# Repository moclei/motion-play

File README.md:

# Motion Play

ESP32-based sensor system for detecting and tracking fast-moving objects through a detection plane. Designed for games and sports performance training.

## Project Status

**Phase 4 - Integration & Polish** (77% complete)

- ✅ Custom PCBs with dual-MUX sensor architecture
- ✅ 1000 Hz data collection with PSRAM buffering
- ✅ AWS IoT Core + Lambda + DynamoDB backend
- ✅ React web interface with visualization and device control
- 🔄 Testing, optimization, documentation

## Repository Structure

```
motion-play/
├── .context/           # AI context documentation (start here)
│   ├── PROJECT.md      # Comprehensive project context
│   ├── manifest.yaml   # Structured metadata
│   └── IDEAS.md        # Feature backlog
├── firmware/           # ESP32-S3 firmware (PlatformIO/Arduino)
├── frontend/           # React web interface
├── lambda/             # AWS Lambda functions
├── infrastructure/     # AWS setup and deployment
├── hardware/           # KiCad PCB designs
│   ├── pcb-main/       # Main controller board
│   ├── sensor-rigid/   # Sensor rigid base (mux, connectors)
│   └── sensor-flex/    # Sensor flex strip (VCNL4040s)
└── docs/references/    # Hardware datasheets
```

## Quick Start

```bash
# Firmware
cd firmware && pio run -t upload

# Frontend
cd frontend/motion-play-ui && npm install && npm run dev
```

## Documentation

**For AI assistants and detailed context**: See [`.context/PROJECT.md`](.context/PROJECT.md)

**Hardware reference materials**: See [`docs/references/`](docs/references/)

## Hardware

- **MCU**: LilyGO T-Display-S3 (ESP32-S3)
- **Sensors**: 6× VCNL4040 proximity sensors (3 assemblies × 2 sensors)
- **Sensor Design**: Rigid+Flex hybrid PCBs (sensors on flex strip angle outward for better direction detection)
- **Architecture**: TCA9548A → PCA9546A → VCNL4040 (dual I2C multiplexing)

## License

[TBD]

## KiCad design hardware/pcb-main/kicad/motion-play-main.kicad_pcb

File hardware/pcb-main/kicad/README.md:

# motion-play-main
Main PCB for Motion Play project

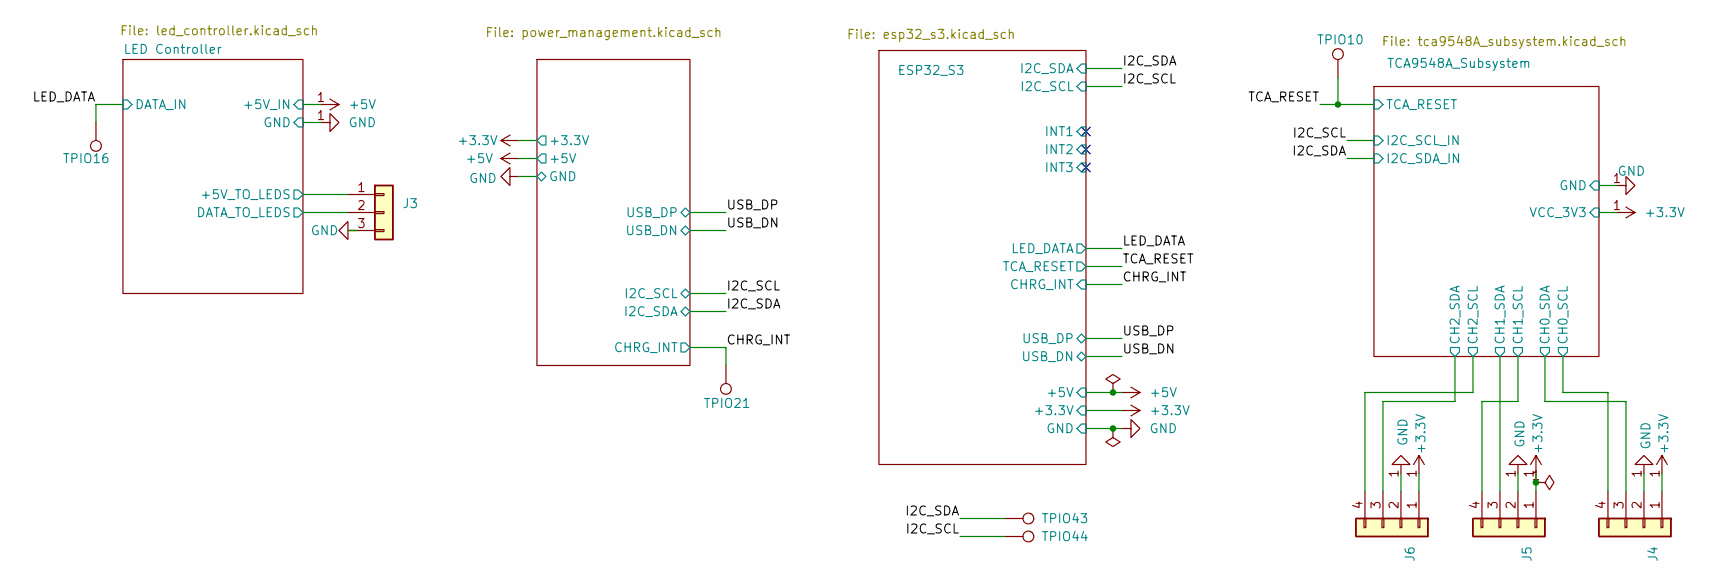
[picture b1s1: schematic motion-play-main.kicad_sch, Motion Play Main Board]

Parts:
J3: LED_Strip; JST_PH_S3B-PH-SM4-TB_1x03-1MP_P2.00mm_Horizontal; LCSC Part C265101
J4, J5, J6: Conn_01x04; JST_SH_SM04B-SRSS-TB_1x04-1MP_P1.00mm_Horizontal; LCSC Part No C160404
TPIO10, TPIO16, TPIO21, TPIO43, TPIO44: TestPoint; TestPoint_Pad_D2.0mm

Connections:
+3.3V: J4.1, J5.1, J6.1; also elsewhere on the board
/CHRG_INT: TPIO21.1; also elsewhere on the board
/I2C_SCL: TPIO44.1; also elsewhere on the board
/I2C_SDA: TPIO43.1; also elsewhere on the board
/LED Controller/+5V_TO_LEDS: J3.1; also elsewhere on the board
/LED Controller/DATA_TO_LEDS: J3.2; also elsewhere on the board
/LED_DATA: TPIO16.1; also elsewhere on the board
/TCA9548A_Subsystem/CH0_SCL: J4.4; also elsewhere on the board
/TCA9548A_Subsystem/CH0_SDA: J4.3; also elsewhere on the board
/TCA9548A_Subsystem/CH1_SCL: J5.4; also elsewhere on the board
/TCA9548A_Subsystem/CH1_SDA: J5.3; also elsewhere on the board
/TCA9548A_Subsystem/CH2_SCL: J6.4; also elsewhere on the board
/TCA9548A_Subsystem/CH2_SDA: J6.3; also elsewhere on the board
/TCA_RESET: TPIO10.1; also elsewhere on the board
GND: J3.3, J4.2, J5.2, J6.2; also elsewhere on the board

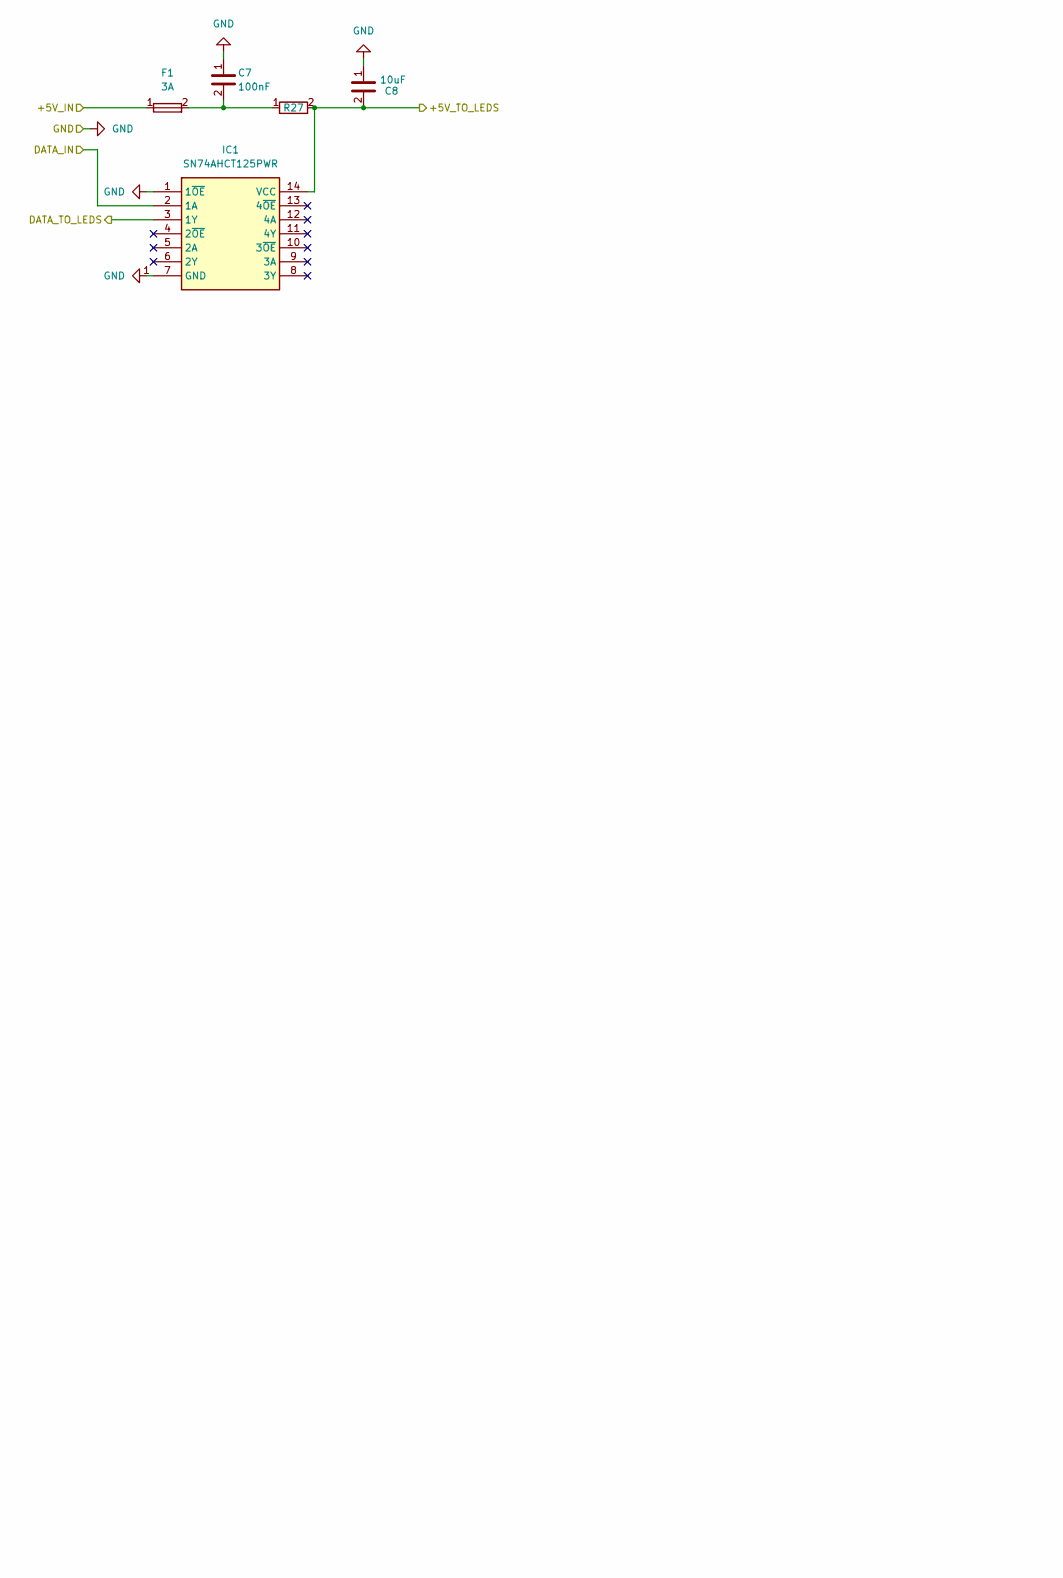
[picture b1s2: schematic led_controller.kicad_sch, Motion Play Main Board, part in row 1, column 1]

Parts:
C7: 100nF; C_0603_1608Metric; LCSC Part No C14663
C8: 10uF; C_0603_1608Metric; LCSC Part No C19702
F1: 3A; Fuse_1206_3216Metric; LCSC Part No C354897
IC1: SN74AHCT125PWR; SOP65P640X120-14N; Mouser Part Number 595-SN74AHCT125PWR
R27: 0.1R; R_2512_6332Metric; LCSC Part No C2903476

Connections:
+5V: F1.1; also elsewhere on the board
/LED Controller/+5V_TO_LEDS: C8.2, IC1.14 (VCC), R27.2; also elsewhere on the board
/LED Controller/DATA_TO_LEDS: IC1.3 (1Y); also elsewhere on the board
/LED_DATA: IC1.2 (1A); also elsewhere on the board
GND: C7.1, C8.1, IC1.1 (1~OE), IC1.7 (GND); also elsewhere on the board
unnamed: C7.2, F1.2, R27.1

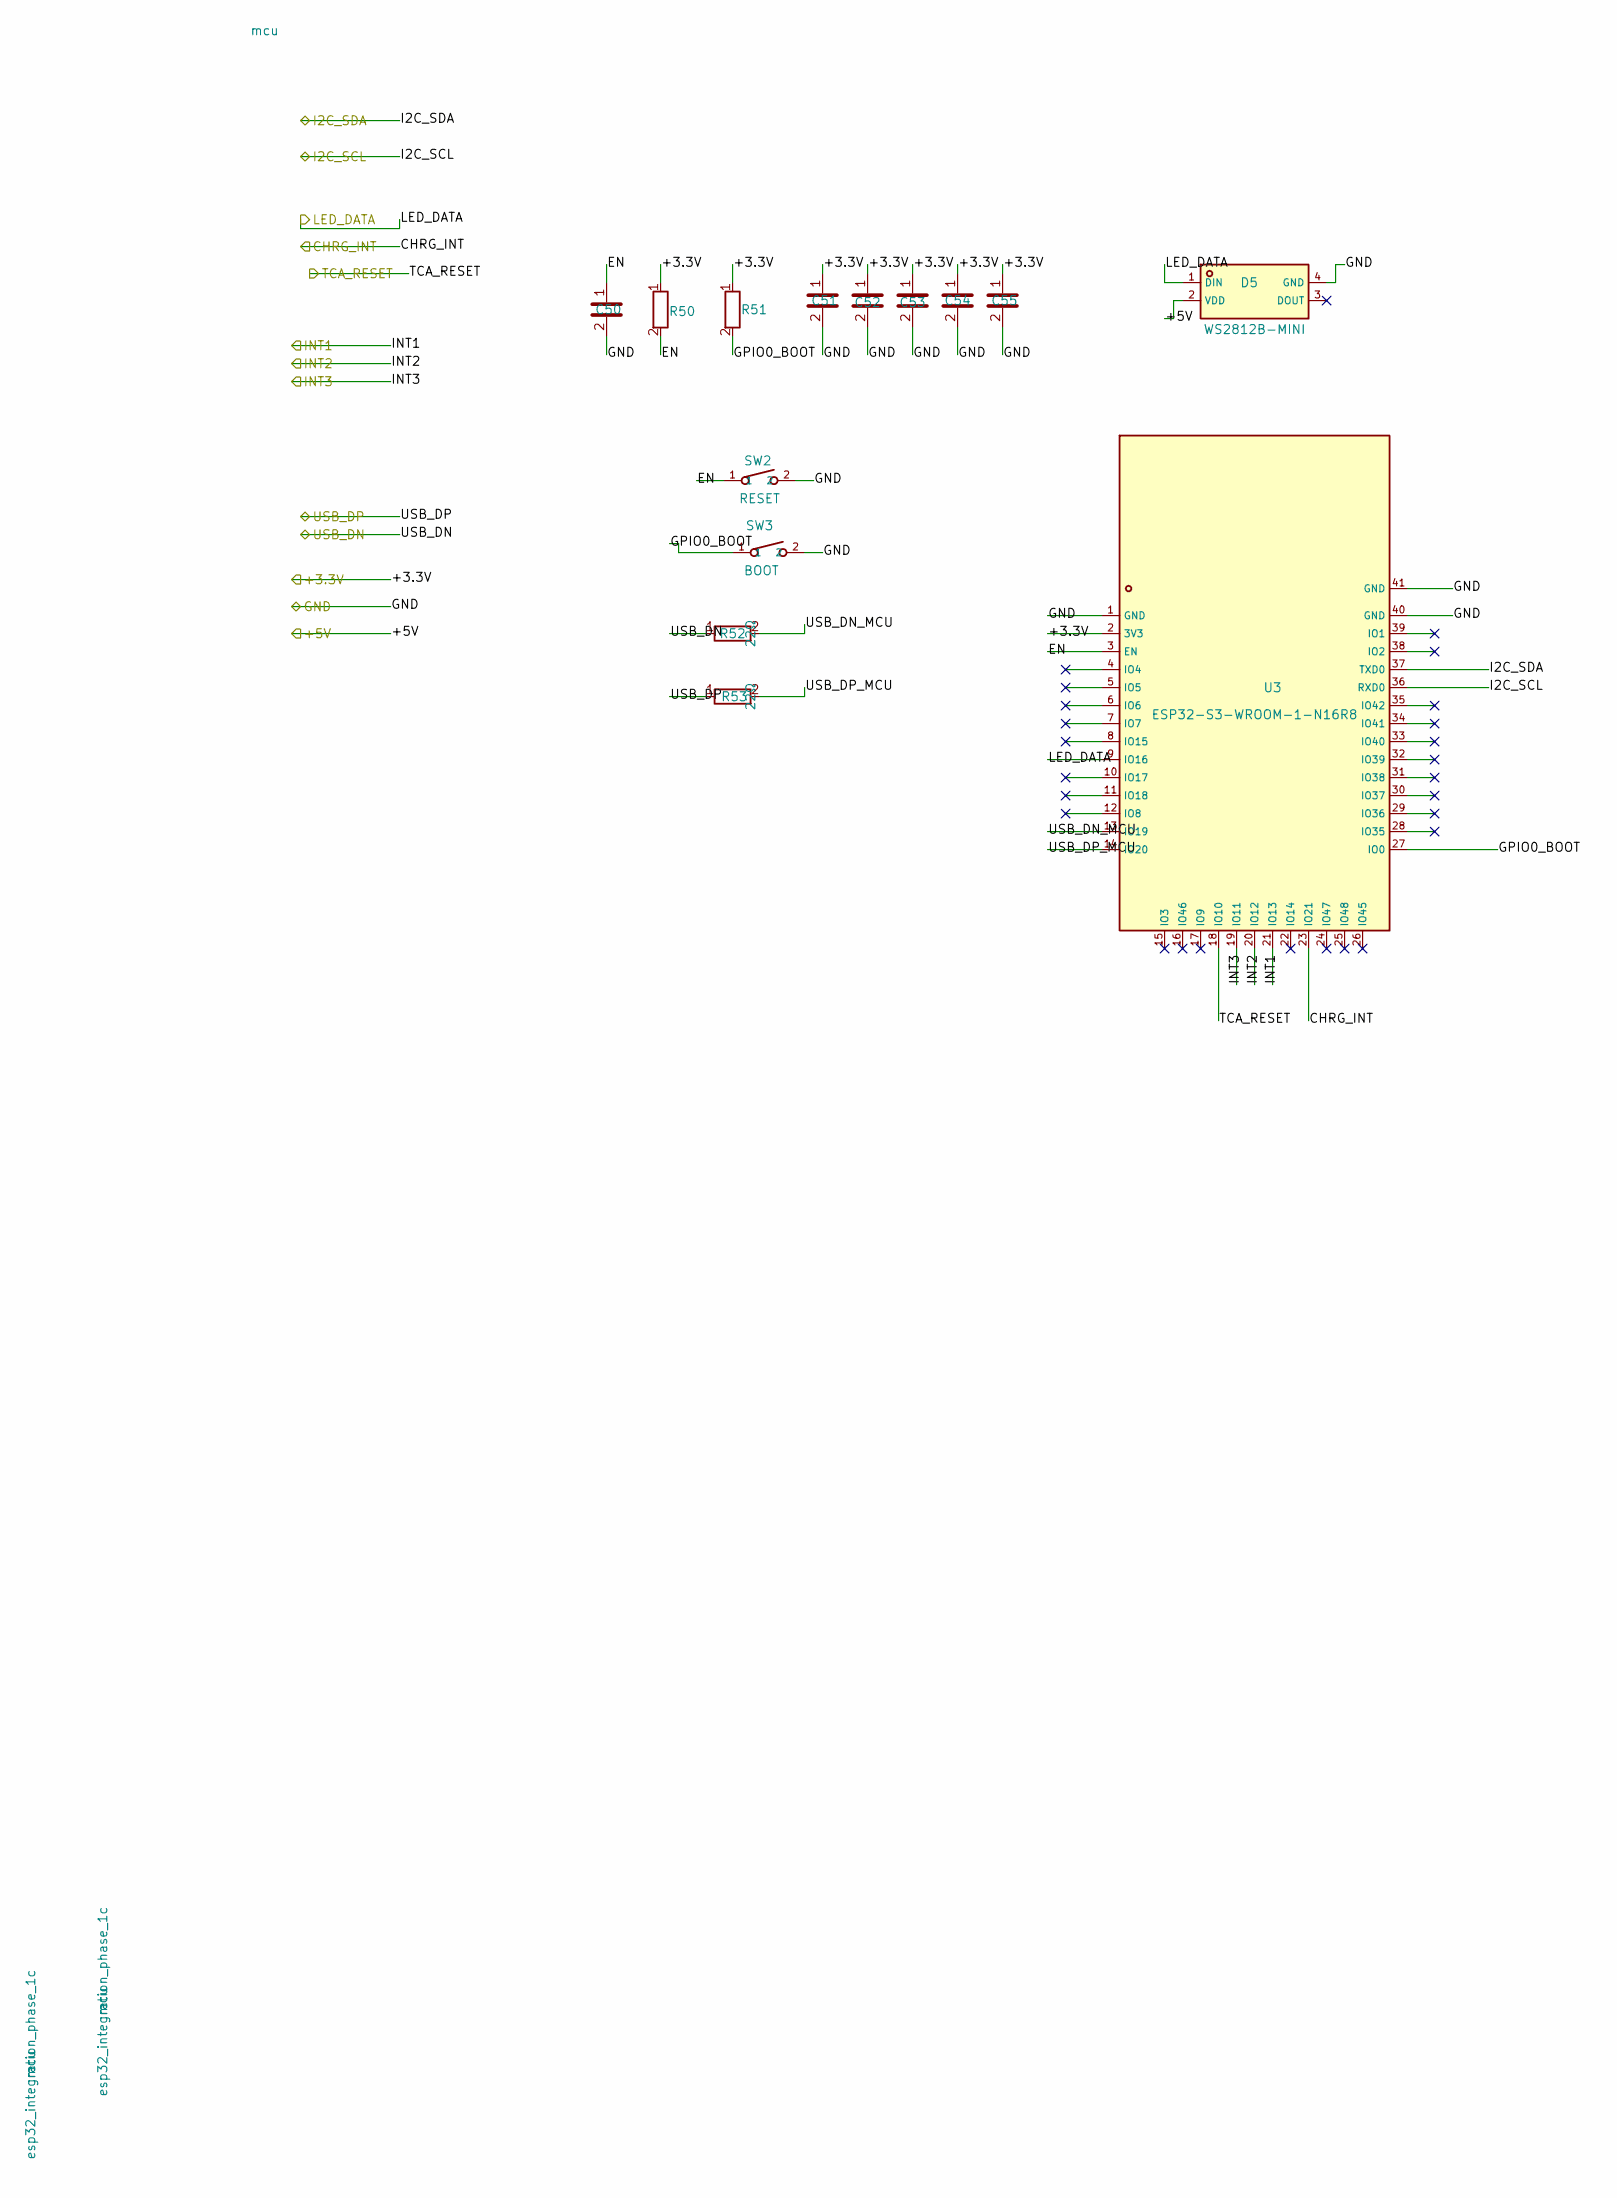
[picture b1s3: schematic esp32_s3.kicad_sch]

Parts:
C50, C55: 1µF; C_0603_1608Metric; LCSC Part C15849
C51: 10µF; C_0603_1608Metric; LCSC Part C96446
C52, C53, C54: 100nF; C_0603_1608Metric; LCSC Part C14663
D5: WS2812B-MINI; LED-SMD_4P-L3.5-W3.5-TL_WS2812B-1; LCSC Part C4154873
R50, R51: 10kΩ; R_0603_1608Metric; LCSC Part C25804
R52, R53: 22Ω; R_0603_1608Metric; LCSC Part C23345
SW2: RESET; KEY-SMD_L4.0-W3.0-LS4.9-1; LCSC Part C49234124
SW3: BOOT; KEY-SMD_L4.0-W3.0-LS4.9-1; LCSC Part C49234124
U3: ESP32-S3-WROOM-1-N16R8; WIRELM-SMD_ESP32-S3-WROOM-1; LCSC Part C2913202

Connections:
+3.3V: C51.1, C52.1, C53.1, C54.1, C55.1, R50.1, R51.1, U3.2 (3V3); also elsewhere on the board
+5V: D5.2 (VDD); also elsewhere on the board
/CHRG_INT: U3.23 (IO21); also elsewhere on the board
/ESP32_S3/EN: C50.1, R50.2, SW2.1, U3.3 (EN)
/ESP32_S3/GPIO0_BOOT: R51.2, SW3.1, U3.27 (IO0)
/ESP32_S3/INT1: U3.21 (IO13)
/ESP32_S3/INT2: U3.20 (IO12)
/ESP32_S3/INT3: U3.19 (IO11)
/ESP32_S3/USB_DN_MCU: R52.2, U3.13 (IO19)
/ESP32_S3/USB_DP_MCU: R53.2, U3.14 (IO20)
/I2C_SCL: U3.36 (RXD0); also elsewhere on the board
/I2C_SDA: U3.37 (TXD0); also elsewhere on the board
/LED_DATA: D5.1 (DIN), U3.9 (IO16); also elsewhere on the board
/TCA_RESET: U3.18 (IO10); also elsewhere on the board
/USB_DN: R52.1; also elsewhere on the board
/USB_DP: R53.1; also elsewhere on the board
GND: C50.2, C51.2, C52.2, C53.2, C54.2, C55.2, D5.4 (GND), SW2.2, SW3.2, U3.1 (GND), U3.40 (GND), U3.41 (GND); also elsewhere on the board

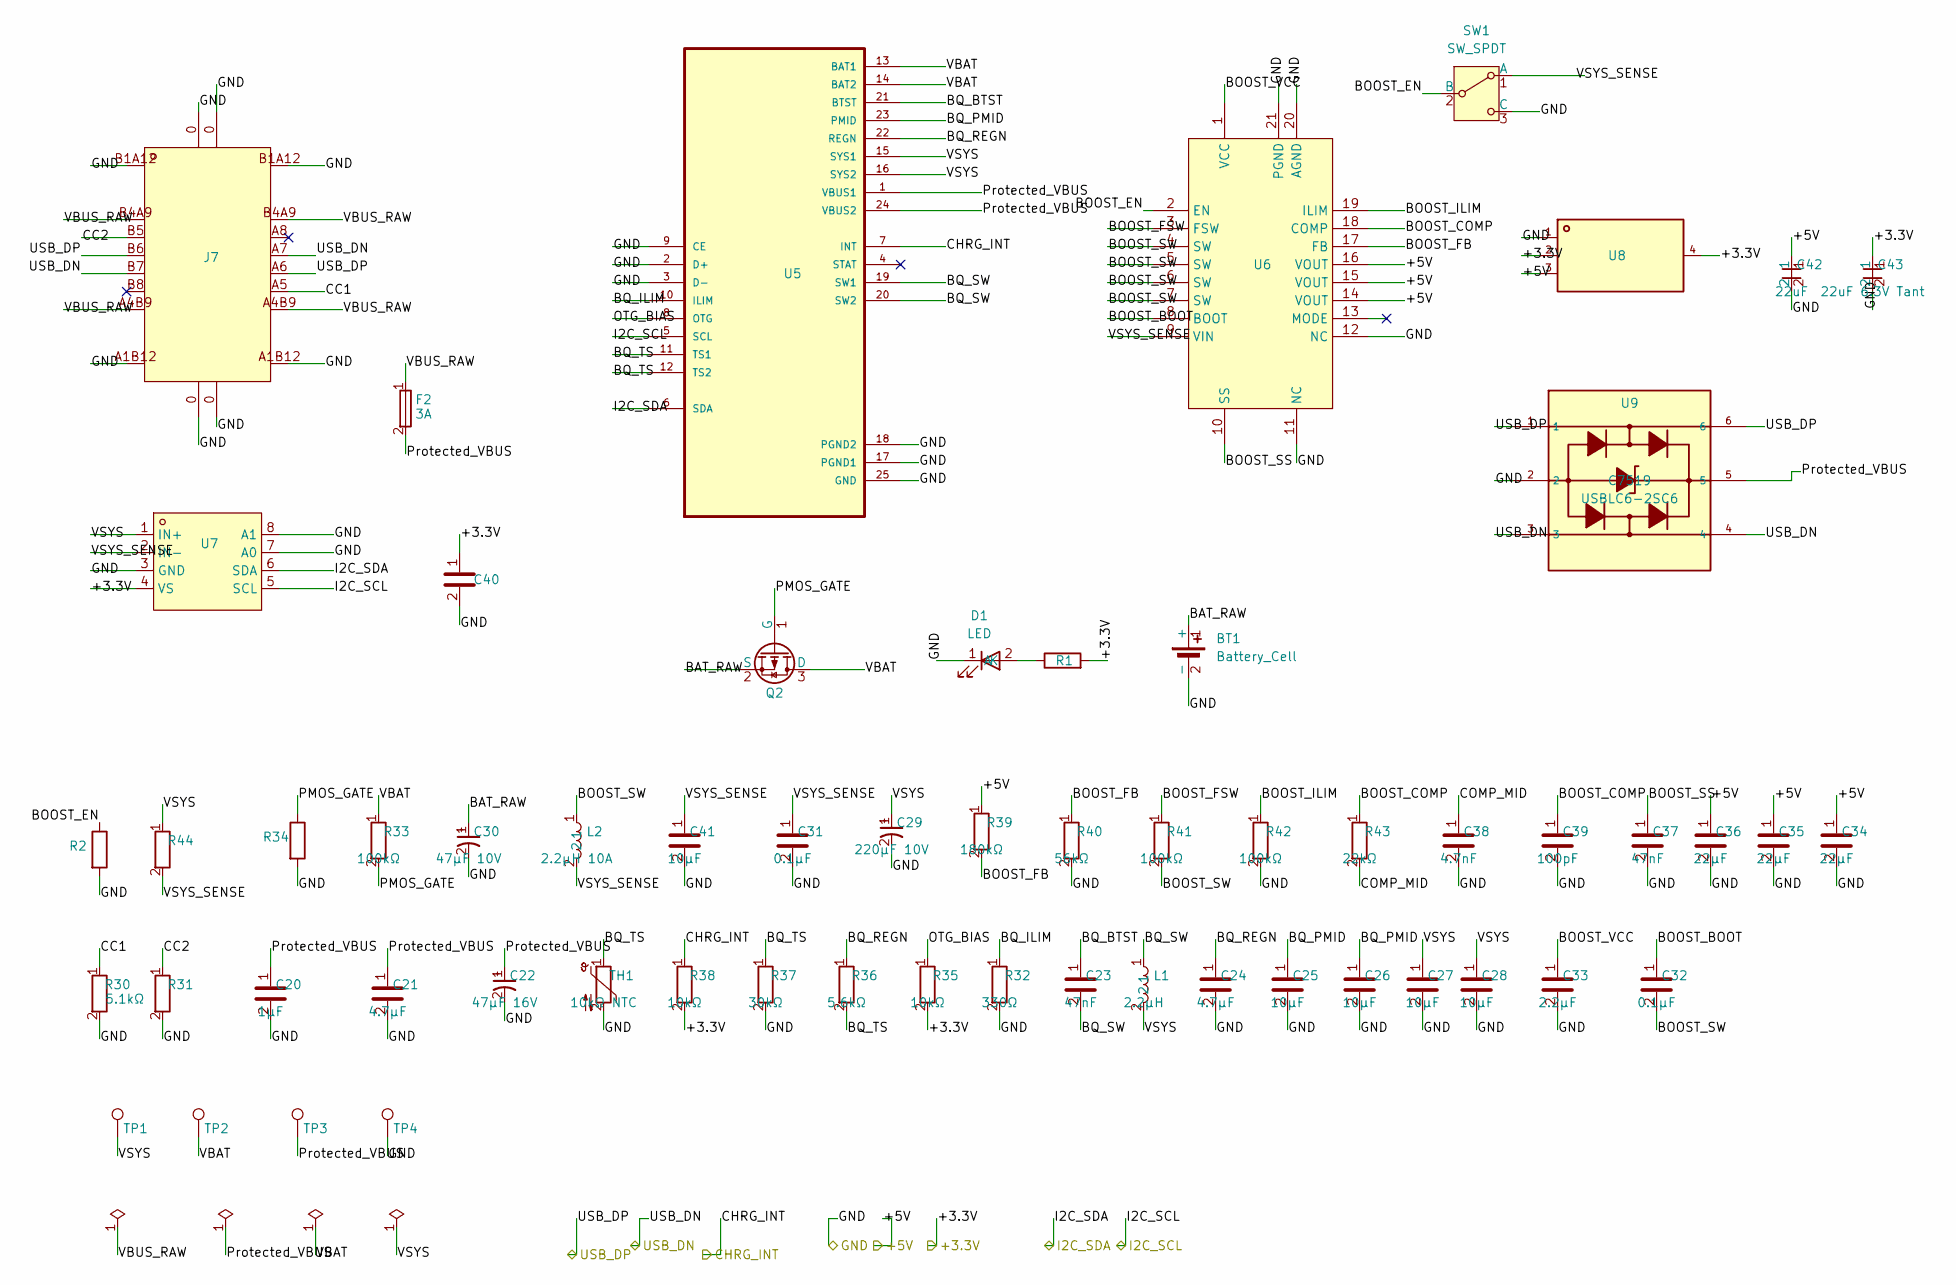
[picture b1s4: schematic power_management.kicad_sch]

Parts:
BT1: Battery_Cell; BatteryHolder_Keystone_1042_1x18650
C20: 1µF; C_0603_1608Metric; LCSC Part C15849
C21, C24: 4.7µF; C_0603_1608Metric; LCSC Part C19666
C22: 47µF 16V; C_Elec_6.3x5.4; LCSC Part C7469958
C23, C37: 47nF; C_0603_1608Metric; LCSC Part C107093
C25, C26, C27, C28: 10µF; C_0603_1608Metric; LCSC Part C96446
C29: 220µF 10V; CP_Elec_6.3x7.7; LCSC Part C3342
C30: 47µF 10V; C_Elec_6.3x5.4; LCSC Part C7469958
C31, C32, C40: 0.1µF; C_0603_1608Metric; LCSC Part C14663
C33: 2.2µF; C_0603_1608Metric; LCSC Part C23630
C34, C35, C36: 22µF; C_0805_2012Metric; LCSC Part C109314
C38: 4.7nF; C_0603_1608Metric; LCSC Part C1621
C39: 100pF; C_0603_1608Metric; LCSC Part C14858
C41: 10µF; C_0805_2012Metric; LCSC Part C15850
C42: 22uF; C0805; LCSC Part C109314
C43: 22uF 6.3V Tant; CASE-A_3216; LCSC Part C129288
D1: LED; LED_0603_1608Metric; LCSC Part C19171301
F2: 3A; Fuse_1206_3216Metric; LCSC Part C2897466
J7: TYPE-C-31-M-12; USB-C_SMD-TYPE-C-31-M-12_1; LCSC Part C165948
L1: 2.2µH; L_Changjiang_FNR6028S; LCSC Part C266426
L2: 2.2µH 10A; IND-SMD_L7.0-W6.6; LCSC Part C167218
Q2: PMOS; SOT-23; LCSC Part C15127
R1: 1kΩ; R_0603_1608Metric; LCSC Part C22548
R2, R33, R34, R41, R42: 100kΩ; R_0603_1608Metric; LCSC Part C14675
R30, R31: 5.1kΩ; R_0603_1608Metric; LCSC Part C23186
R32: 330Ω; R_0603_1608Metric; LCSC Part C23138
R35, R38: 10kΩ; R_0603_1608Metric; LCSC Part C25804
R36: 5.6kΩ; R_0603_1608Metric; LCSC Part C23189
R37: 30kΩ; R_0603_1608Metric; LCSC Part C22984
R39: 180kΩ; R_0603_1608Metric; LCSC Part C22827
R40: 56kΩ; R_0603_1608Metric; LCSC Part C23206
R43: 22kΩ; R_0603_1608Metric; LCSC Part C31850
R44: 10mΩ; R_2512_6332Metric; LCSC Part C1322424
SW1: SW_SPDT; MK-12C02-G020_GSW; LCSC Part C431540
TH1: 10kΩ NTC; R_0603_1608Metric; LCSC Part C13564
TP1: VSYS; TestPoint_Pad_D1.5mm
TP2: VBAT; TestPoint_Pad_D1.5mm
TP3: PVBUS; TestPoint_Pad_D1.5mm
TP4: PGND; TestPoint_Pad_D1.5mm
U5: BQ24195RGER; VQFN-24_L4.0-W4.0-P0.50-TL-EP2.8; LCSC Part C90862
U6: TPS61088RHLR; VQFN-20_L4.6-W3.6-P0.50-BL; LCSC Part C87357
U7: INA219AIDCNR; SOT-23-8_L3.0-W1.7-P0.65-LS2.8-BR; LCSC Part C87469
U8: AMS1117-3.3; SOT-223-3_L6.5-W3.4-P2.30-LS7.0-BR; LCSC Part C6186
U9: USBLC6-2SC6; SOT-23-6_L2.9-W1.6-P0.95-LS2.8-BL; LCSC Part C7519

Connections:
+3.3V: C40.1, C43.1, R1.2, R35.2, R38.2, U7.4 (VS), U8.2 (VOUT), U8.4 (VOUT); also elsewhere on the board
+5V: C34.1, C35.1, C36.1, C42.1, R39.1, U6.14 (VOUT), U6.15 (VOUT), U6.16 (VOUT), U8.3 (VIN); also elsewhere on the board
/CHRG_INT: R38.1, U5.7 (INT); also elsewhere on the board
/I2C_SCL: U5.5 (SCL), U7.5 (SCL); also elsewhere on the board
/I2C_SDA: U5.6 (SDA), U7.6 (SDA); also elsewhere on the board
/Power Management/BAT_RAW: BT1.1 (+), C30.1, Q2.2 (S)
/Power Management/BOOST_BOOT: C32.1, U6.8 (BOOT)
/Power Management/BOOST_COMP: C39.1, R43.1, U6.18 (COMP)
/Power Management/BOOST_EN: R2.1, SW1.2 (B), U6.2 (EN)
/Power Management/BOOST_FB: R39.2, R40.1, U6.17 (FB)
/Power Management/BOOST_FSW: R41.1, U6.3 (FSW)
/Power Management/BOOST_ILIM: R42.1, U6.19 (ILIM)
/Power Management/BOOST_SS: C37.1, U6.10 (SS)
/Power Management/BOOST_SW: C32.2, L2.1, R41.2, U6.4 (SW), U6.5 (SW), U6.6 (SW), U6.7 (SW)
/Power Management/BOOST_VCC: C33.1, U6.1 (VCC)
/Power Management/BQ_BTST: C23.1, U5.21 (BTST)
/Power Management/BQ_ILIM: R32.1, U5.10 (ILIM)
/Power Management/BQ_PMID: C25.1, C26.1, U5.23 (PMID)
/Power Management/BQ_REGN: C24.1, R36.1, U5.22 (REGN)
/Power Management/BQ_SW: C23.2, L1.1, U5.19 (SW1), U5.20 (SW2)
/Power Management/BQ_TS: R36.2, R37.1, TH1.1, U5.11 (TS1), U5.12 (TS2)
/Power Management/CC1: J7.A5 (CC1), R30.1
/Power Management/CC2: J7.B5 (CC2), R31.1
/Power Management/COMP_MID: C38.1, R43.2
/Power Management/OTG_BIAS: R35.1, U5.8 (OTG)
/Power Management/PMOS_GATE: Q2.1 (G), R33.2, R34.1
/Power Management/Protected_VBUS: C20.1, C21.1, C22.1, F2.2, TP3.1, U5.1 (VBUS1), U5.24 (VBUS2), U9.5
/Power Management/VBAT: Q2.3 (D), R33.1, TP2.1, U5.13 (BAT1), U5.14 (BAT2)
/Power Management/VBUS_RAW: F2.1, J7.A4B9 (VBUS), J7.B4A9 (VBUS)
/Power Management/VSYS: C27.1, C28.1, C29.1, L1.2, R44.1, TP1.1, U5.15 (SYS1), U5.16 (SYS2), U7.1 (IN+)
/Power Management/VSYS_SENSE: C31.1, C41.1, L2.2, R44.2, SW1.1 (A), U6.9 (VIN), U7.2 (IN-)
/USB_DN: J7.A7 (DN1), J7.B7 (DN2), U9.3, U9.4; also elsewhere on the board
/USB_DP: J7.A6 (DP1), J7.B6 (DP2), U9.1, U9.6; also elsewhere on the board
GND: BT1.2 (-), C20.2, C21.2, C22.2, C24.2, C25.2, C26.2, C27.2, C28.2, C29.2, C30.2, C31.2, C33.2, C34.2, C35.2, C36.2, C37.2, C38.2, C39.2, C40.2, C41.2, C42.2, C43.2, D1.1 (K), J7.0 (SH), J7.A1B12 (GND), J7.B1A12 (GND), R2.2, R30.2, R31.2, R32.2, R34.2, R37.2, R40.2, R42.2, SW1.3 (C), TH1.2, TP4.1, U5.2 (D+), U5.3 (D-), U5.9 (CE), U5.17 (PGND1), U5.18 (PGND2), U5.25 (GND), U6.11 (NC), U6.12 (NC), U6.20 (AGND), U6.21 (PGND), U7.3 (GND), U7.7 (A0), U7.8 (A1), U8.1 (GND), U9.2; also elsewhere on the board
unnamed: D1.2 (A), R1.1

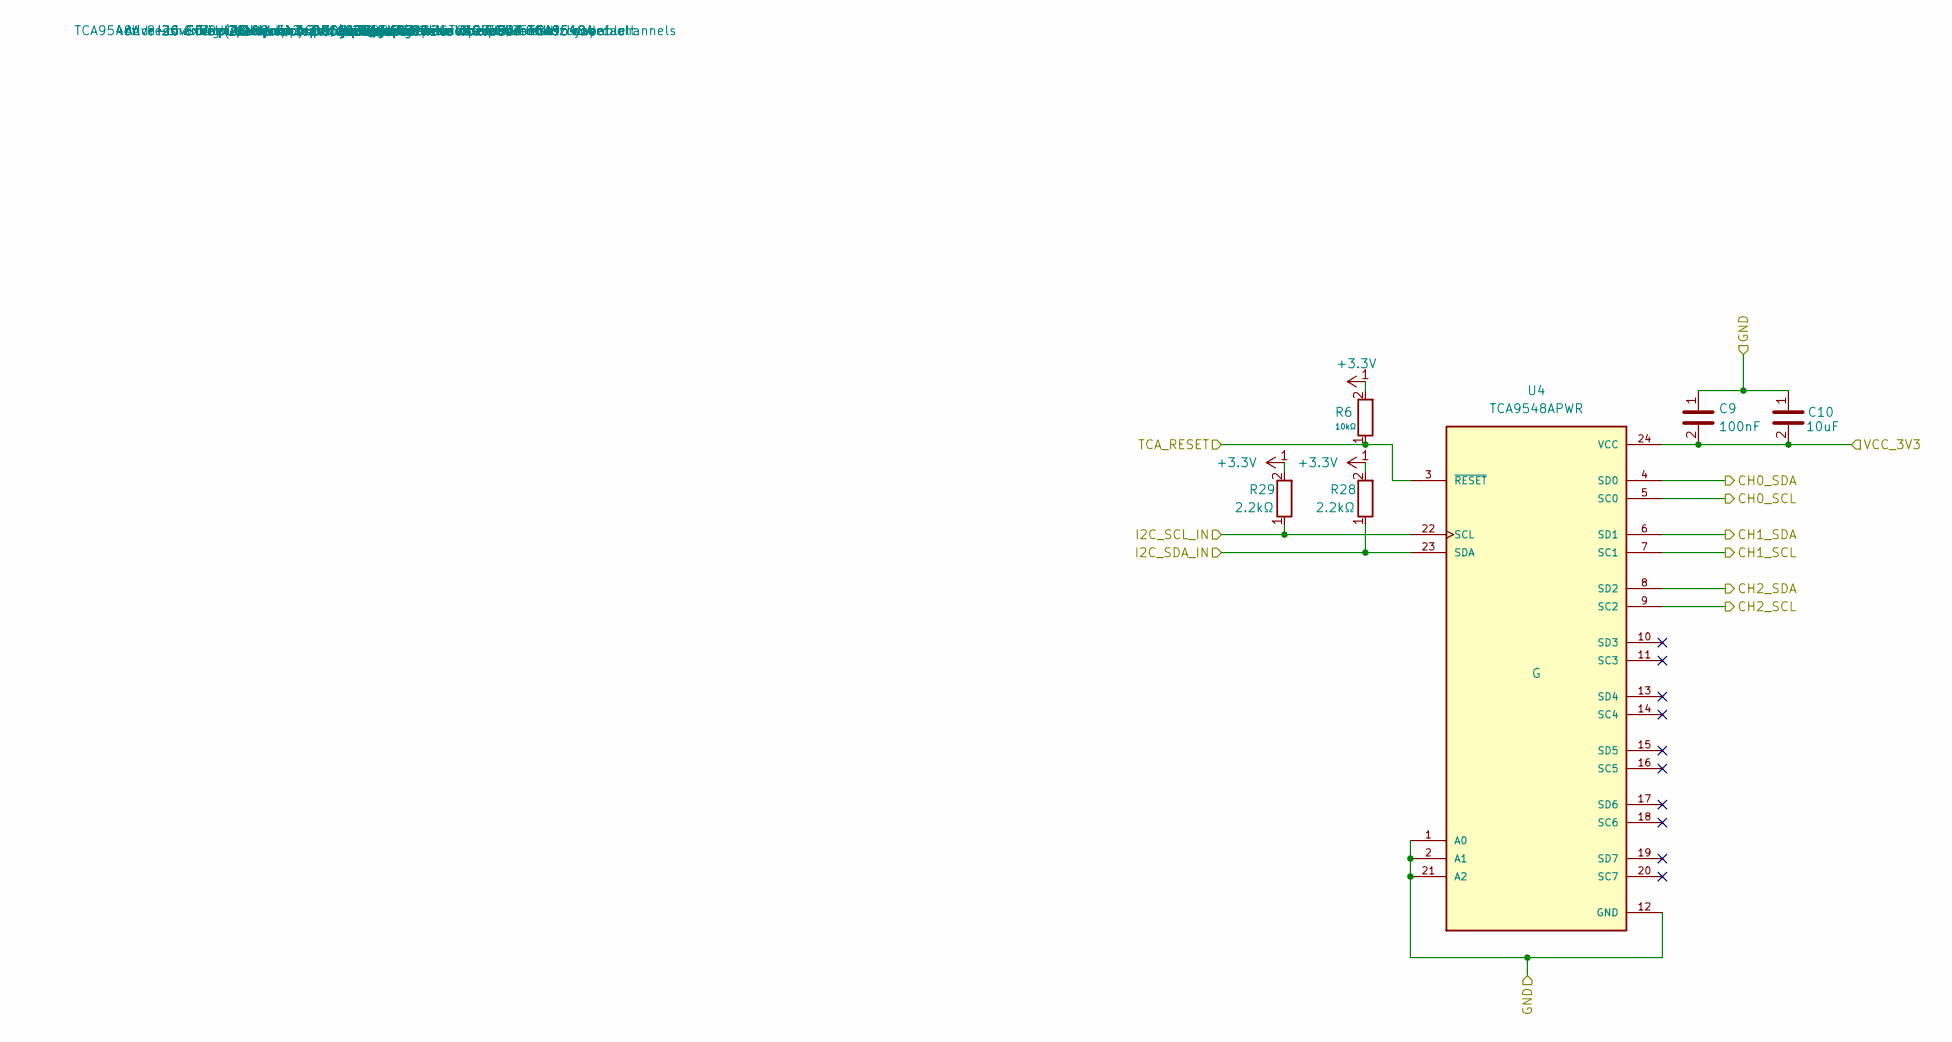
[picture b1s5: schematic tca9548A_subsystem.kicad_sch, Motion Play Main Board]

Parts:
C9: 100nF; C_0603_1608Metric; LCSC Part No C14663
C10: 10uF; C_0603_1608Metric; LCSC Part No C19702
R6: 10kΩ; R_0603_1608Metric; LCSC Part C25804
R28, R29: 2.2kΩ; R_0603_1608Metric; LCSC Part No C114662
U4: TCA9548APWR; SOP65P640X120-24N; PARTREV G; LCSC Part C130026

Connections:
+3.3V: C9.2, C10.2, R6.2, R28.2, R29.2, U4.24 (VCC); also elsewhere on the board
/I2C_SCL: R29.1, U4.22 (SCL); also elsewhere on the board
/I2C_SDA: R28.1, U4.23 (SDA); also elsewhere on the board
/TCA9548A_Subsystem/CH0_SCL: U4.5 (SC0); also elsewhere on the board
/TCA9548A_Subsystem/CH0_SDA: U4.4 (SD0); also elsewhere on the board
/TCA9548A_Subsystem/CH1_SCL: U4.7 (SC1); also elsewhere on the board
/TCA9548A_Subsystem/CH1_SDA: U4.6 (SD1); also elsewhere on the board
/TCA9548A_Subsystem/CH2_SCL: U4.9 (SC2); also elsewhere on the board
/TCA9548A_Subsystem/CH2_SDA: U4.8 (SD2); also elsewhere on the board
/TCA_RESET: R6.1, U4.3 (~RESET); also elsewhere on the board
GND: C9.1, C10.1, U4.1 (A0), U4.2 (A1), U4.12 (GND), U4.21 (A2); also elsewhere on the board

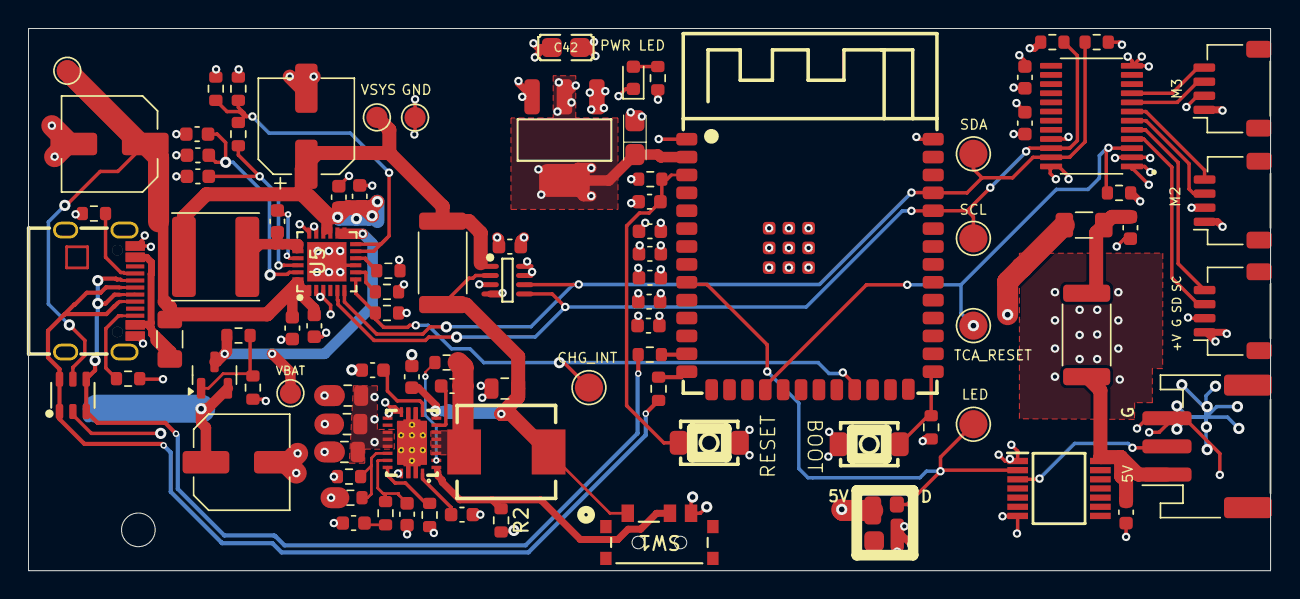
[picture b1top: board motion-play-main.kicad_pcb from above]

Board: 4 copper layers, 88.2 x 38.5 mm, 93 parts (1 on the bottom side), 50 nets.

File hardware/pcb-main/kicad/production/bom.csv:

Designator,Footprint,Quantity,Value,LCSC Part #
"C10, C8",0603,2,10uF,C19702
"C20, C50, C55",0603,3,1µF,C15849
"C21, C24",0603,2,4.7µF,C19666
C22,C_Elec_6.3x5.4,1,47µF 16V,C7469958
"C23, C37",0603,2,47nF,C107093
"C25, C26, C27, C28, C51",0603,5,10µF,C96446
C29,CP_Elec_6.3x7.7,1,220µF 10V,C3342
C30,C_Elec_6.3x5.4,1,47µF 10V,C7469958
"C31, C32, C40",0603,3,0.1µF,C14663
C33,0603,1,2.2µF,C23630
"C34, C35, C36",0805,3,22µF,C109314
C38,0603,1,4.7nF,C1621
C39,0603,1,100pF,C14858
C41,0805,1,10µF,C15850
C42,C0805,1,22uF,C109314
C43,CASE-A_3216,1,22uF 6.3V Tant,C129288
"C52, C53, C54, C7, C9",0603,5,100nF,C14663
D1,0603,1,LED,C19171301
D5,LED-SMD_4P-L3.5-W3.5-TL_WS2812B-1,1,WS2812B-MINI,C4154873
F1,1206,1,3A,C354897
F2,1206,1,3A,C2897466
IC1,SOP65P640X120-14N,1,SN74AHCT125PWR,C36365
J3,JST_PH_S3B-PH-SM4-TB_1x03-1MP_P2.00mm_Horizontal,1,LED_Strip,C265101
"J4, J5, J6",JST_SH_SM04B-SRSS-TB_1x04-1MP_P1.00mm_Horizontal,3,Conn_01x04,C160404
J7,USB-C_SMD-TYPE-C-31-M-12_1,1,TYPE-C-31-M-12,C165948
L1,L_Changjiang_FNR6028S,1,2.2µH,C266426
L2,IND-SMD_L7.0-W6.6,1,2.2µH 10A,C167218
Q2,SOT-23,1,PMOS,C15127
R1,0603,1,1kΩ,C22548
"R2, R33, R34, R41, R42",0603,5,100kΩ,C14675
R27,2512,1,0.1R,C2903476
"R28, R29",0603,2,2.2kΩ,C114662
"R30, R31",0603,2,5.1kΩ,C23186
R32,0603,1,330Ω,C23138
"R35, R38, R50, R51, R6",0603,5,10kΩ,C25804
R36,0603,1,5.6kΩ,C23189
R37,0603,1,30kΩ,C22984
R39,0603,1,180kΩ,C22827
R40,0603,1,56kΩ,C23206
R43,0603,1,22kΩ,C31850
R44,2512,1,10mΩ,C1322424
"R52, R53",0603,2,22Ω,C23345
SW1,MK-12C02-G020_GSW,1,SW_SPDT,C431540
SW2,KEY-SMD_L4.0-W3.0-LS4.9-1,1,RESET,C49234124
SW3,KEY-SMD_L4.0-W3.0-LS4.9-1,1,BOOT,C49234124
TH1,0603,1,10kΩ NTC,C13564
TP1,TestPoint_Pad_D1.5mm,1,VSYS,
TP2,TestPoint_Pad_D1.5mm,1,VBAT,
TP3,TestPoint_Pad_D1.5mm,1,PVBUS,
TP4,TestPoint_Pad_D1.5mm,1,PGND,
"TPIO10, TPIO16, TPIO21, TPIO43, TPIO44",TestPoint_Pad_D2.0mm,5,TestPoint,
U3,WIRELM-SMD_ESP32-S3-WROOM-1,1,ESP32-S3-WROOM-1-N16R8,C2913202
U4,SOP65P640X120-24N,1,TCA9548APWR,C130026
U5,VQFN-24_L4.0-W4.0-P0.50-TL-EP2.8,1,BQ24195RGER,C90862
U6,VQFN-20_L4.6-W3.6-P0.50-BL,1,TPS61088RHLR,C87357
U7,SOT-23-8_L3.0-W1.7-P0.65-LS2.8-BR,1,INA219AIDCNR,C87469
U8,SOT-223-3_L6.5-W3.4-P2.30-LS7.0-BR,1,AMS1117-3.3,C6186
U9,SOT-23-6_L2.9-W1.6-P0.95-LS2.8-BL,1,USBLC6-2SC6,C7519

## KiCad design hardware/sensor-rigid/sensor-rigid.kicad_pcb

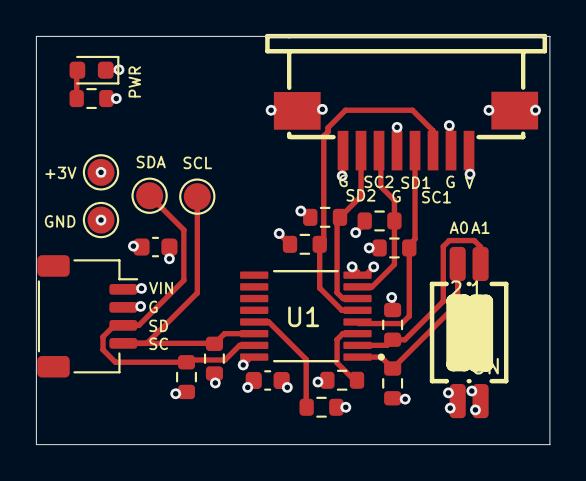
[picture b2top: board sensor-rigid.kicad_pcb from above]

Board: 4 copper layers, 28.5 x 22.7 mm, 22 parts (0 on the bottom side), 13 nets.

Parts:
C1: 2.2µF; C_0603_1608Metric
C2: 0.1µF; C_0603_1608Metric
D1: LED; LED_0603_1608Metric
FPC1: FPC1.0-8P; FPC-SMD_8P-P1.00_FPC1.0-8P-SJ
J1: Conn_01x04; JST_SH_SM04B-SRSS-TB_1x04-1MP_P1.00mm_Horizontal
R1, R2, R6, R7, R8, R9: 4.7kΩ; R_0603_1608Metric
R3, R12, R13, R14: 10kΩ; R_0603_1608Metric
R4: 1kΩ; R_0603_1608Metric
SW1: EP-02KS; SW-SMD_EP-02KS
TP1: 3V3; TestPoint_Pad_D1.5mm
TP2: GND; TestPoint_Pad_D1.5mm
TP3: SDA_UP; TestPoint_Pad_D1.5mm
TP4: SCL_UP; TestPoint_Pad_D1.5mm
U1: PCA9546APWR; SOP65P640X120-16N

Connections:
+3.3V: C1.2, C2.2, FPC1.1 (3.3V), J1.1, R1.1, R2.1, R3.2, R4.2, R6.1, R7.1, R8.2, R9.2, R12.2, SW1.3 (B2), SW1.4 (B1), TP1.1, U1.16 (VDD)
/LED_A: D1.2 (A), R4.1
/PCA_A0: R13.2, SW1.2 (A2), U1.1 (A0)
/PCA_A1: R14.2, SW1.1 (A1), U1.2 (A1)
/PCA_A2: R12.1, U1.13 (A2)
/PCA_RESET: R3.1, U1.3 (~RESET)
/SCL1: FPC1.3 (SCL1), R9.1, U1.5 (SC0)
/SCL2: FPC1.6 (SCL2), R7.2, U1.7 (SC1)
/SCL_UP: J1.4, R2.2, TP4.1, U1.14 (SCL)
/SDA1: FPC1.4 (SDA1), R8.1, U1.4 (SD0)
/SDA2: FPC1.7 (SDA2), R6.2, U1.6 (SD1)
/SDA_UP: J1.3, R1.2, TP3.1, U1.15 (SDA)
GND: C1.1, C2.1, D1.1 (K), FPC1.2 (GND), FPC1.5 (GND), FPC1.8 (GND), FPC1.9 (GND), FPC1.10 (GND), J1.2, R13.1, R14.1, TP2.1, U1.8 (VSS)

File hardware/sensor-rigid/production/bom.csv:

Designator,Footprint,Quantity,Value,LCSC Part #
C1,0603,1,2.2µF,C23630
C2,0603,1,0.1µF,C14663
D1,0603,1,LED,C19171301
"D2, D3",SOT-23,2,BAT54S,C727126
FPC1,FPC-SMD_8P-P1.00_FPC1.0-8P-SJ,1,FPC1.0-8P,C132510
J1,JST_SH_SM05B-SRSS-TB_1x05-1MP_P1.00mm_Horizontal,1,Conn_01x05,C136657
"R1, R2, R6, R7, R8, R9",0603,6,4.7kΩ,C99782
"R12, R13, R14, R3",0603,4,10kΩ,C25804
R4,0603,1,1kΩ,C22548
R5,0603,1,8.2kΩ,C25981
"TP1, TP2, TP3, TP4, TP5",TestPoint_Pad_D1.5mm,5,TestPoint_Small,
U1,SOP65P640X120-16N,1,PCA9546APWR,C400705

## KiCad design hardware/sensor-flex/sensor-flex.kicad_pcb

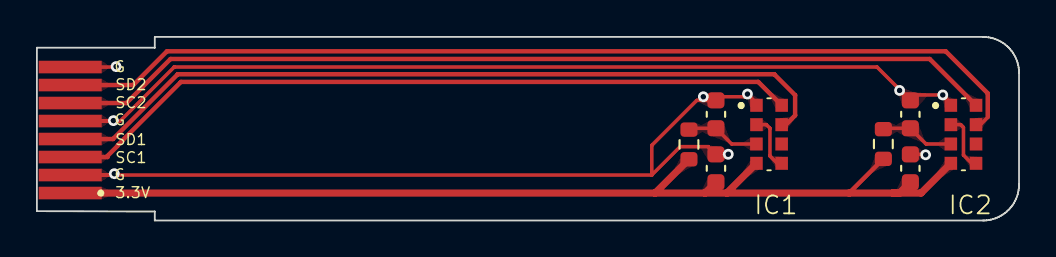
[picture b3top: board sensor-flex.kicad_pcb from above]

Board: 2 copper layers, 54.6 x 10.2 mm, 9 parts (0 on the bottom side), 10 nets.

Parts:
C4, C8: 2.2µF; C_0603_1608Metric
C6, C7: 0.1µF; C_0603_1608Metric
FPC1: FPC_Tail_10P; FPC_Tail_10P_1.0mm_TopContact
IC1, IC2: VCNL4040M3OE
R10, R11: 22Ω; R_0603_1608Metric

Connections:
+3.3V: C4.2, C8.2, FPC1.1 (3.3V), IC1.4 (A), IC2.4 (A), R10.2, R11.1
/LED_K1: IC1.2 (K(SENSOR)), IC1.5 (K(LED))
/LED_K2: IC2.2 (K(SENSOR)), IC2.5 (K(LED))
/SCL1: FPC1.3 (SCL1), IC1.8 (SCLK)
/SCL2: FPC1.6 (SCL2), IC2.8 (SCLK)
/SDA1: FPC1.4 (SCL2), IC1.7 (SDAT)
/SDA2: FPC1.7 (SDA2), IC2.7 (SDAT)
/VDD_S1: C7.1, IC1.3 (VDD), R11.2
/VDD_S2: C6.1, IC2.3 (VDD), R10.1
GND: C4.1, C6.2, C7.2, C8.1, FPC1.2 (GND), FPC1.5 (GND), FPC1.8 (GND), IC1.1 (GND), IC2.1 (GND)
